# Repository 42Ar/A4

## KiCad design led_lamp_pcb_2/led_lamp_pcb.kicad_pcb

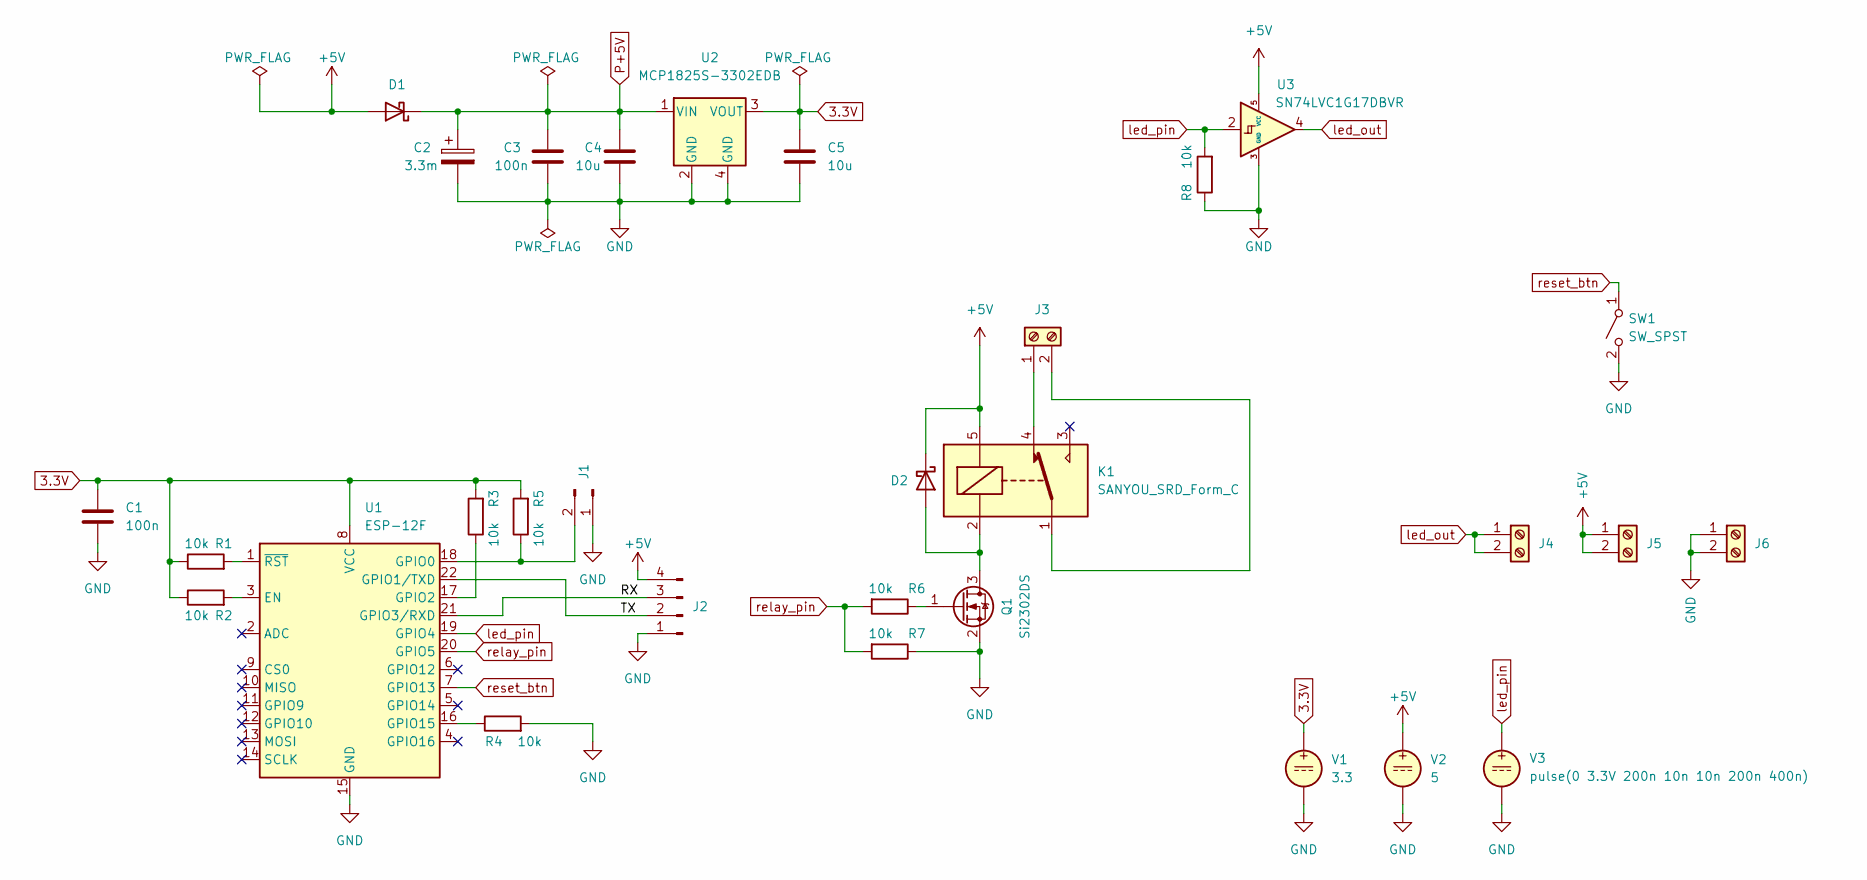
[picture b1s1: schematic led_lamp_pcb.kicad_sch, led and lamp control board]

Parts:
C1, C3: 100n; C_0805_2012Metric_Pad1.18x1.45mm_HandSolder
C2: 3.3m; CP_Radial_D10.0mm_P5.00mm
C4, C5: 10u; C_0805_2012Metric_Pad1.18x1.45mm_HandSolder
D1, D2: 1N5817; D_SMA_Handsoldering
J1: Conn_01x02_Male; PinHeader_1x02_P2.54mm_Vertical
J2: Conn_01x04_Male; PinHeader_1x04_P2.54mm_Vertical
J3, J4, J5, J6: Screw_Terminal_01x02; TerminalBlock_bornier-2_P5.08mm
K1: SANYOU_SRD_Form_C; Relay_SPDT_SANYOU_SRD_Series_Form_C
Q1: Si2302DS; SOT-23_Handsoldering
R1, R2, R3, R4, R5, R6, R7, R8: 10k; R_0805_2012Metric_Pad1.20x1.40mm_HandSolder
SW1: SW_SPST; SW_Push_1P1T_NO_6x6mm_H9.5mm
U1: ESP-12F; ESP-12E
U2: MCP1825S-3302EDB; SOT-223
U3: SN74LVC1G17DBVR; SOT-23-5_HandSoldering
V1, V2, V3: VDC

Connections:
3.3V: C1.1, C5.1, R1.1, R2.1, R3.2, R5.2, U1.8 (VCC), U2.3 (VOUT), V1.1
+5V: D1.2 (A), D2.1 (K), J2.4, J5.1, J5.2, K1.5, U3.5 (VCC), V2.1
/RX: J2.3, U1.21 (GPIO3/RXD)
/TX: J2.2, U1.22 (GPIO1/TXD)
GND: C1.2, C2.2, C3.2, C4.2, C5.2, J1.1, J2.1, J6.1, J6.2, Q1.2 (S), R4.2, R7.1, R8.1, SW1.2 (B), U1.15 (GND), U2.2 (GND), U2.4 (GND), U3.3 (GND), V1.2, V2.2, V3.2
unnamed: D2.2 (A), K1.2, Q1.3 (D)
unnamed: J1.2, R5.1, U1.18 (GPIO0)
unnamed: J3.1, K1.4
unnamed: J3.2, K1.1
unnamed: Q1.1 (G), R6.1
unnamed: R1.2, U1.1 (~RST)
unnamed: R2.2, U1.3 (EN)
unnamed: R3.1, U1.17 (GPIO2)
unnamed: R4.1, U1.16 (GPIO15)
P+5V: C2.1, C3.1, C4.1, D1.1 (K), U2.1 (VIN)
led_out: J4.1, J4.2, U3.4
led_pin: R8.2, U1.19 (GPIO4), U3.2, V3.1
relay_pin: R6.2, R7.2, U1.20 (GPIO5)
reset_btn: SW1.1 (A), U1.7 (GPIO13)

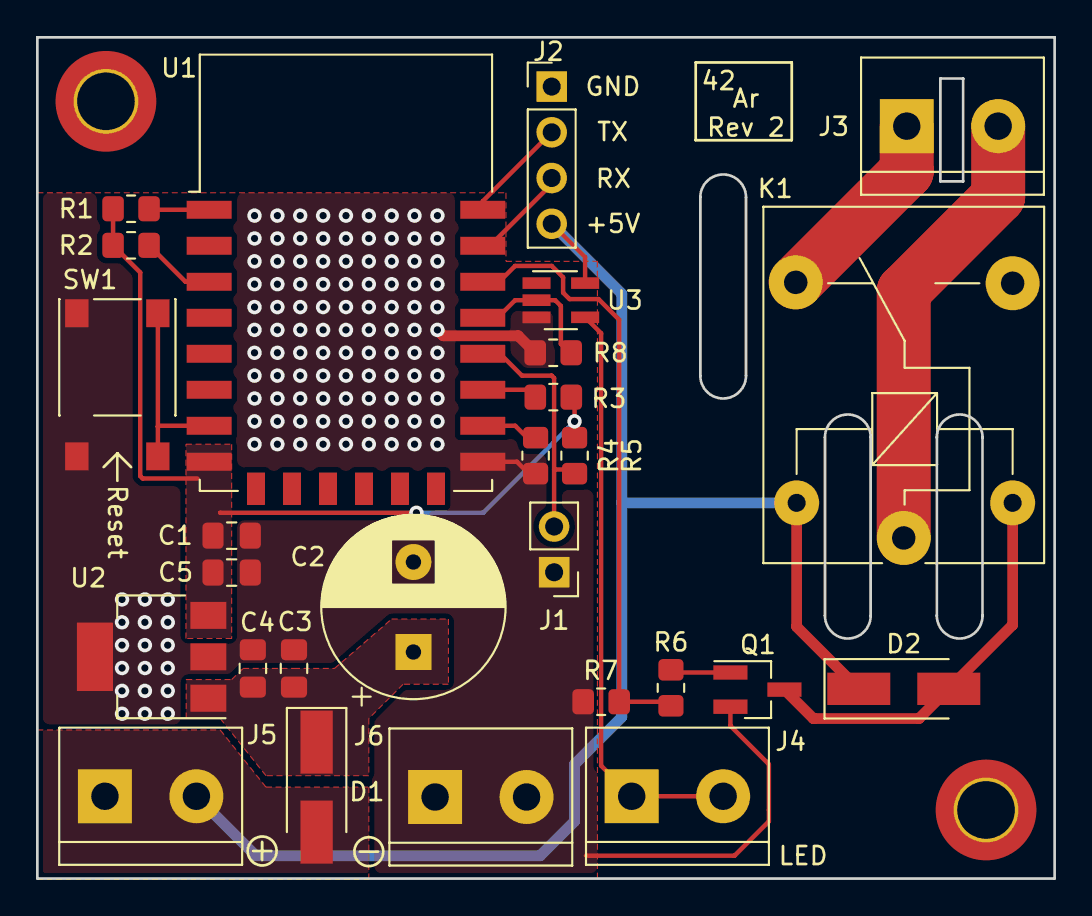
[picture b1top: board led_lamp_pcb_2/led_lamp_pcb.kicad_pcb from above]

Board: 2 copper layers, 56.5 x 46.7 mm, 29 parts (0 on the bottom side), 19 nets.

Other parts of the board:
H1, H2: MountingHole_3.2mm_M3_DIN965_Pad_TopBottom

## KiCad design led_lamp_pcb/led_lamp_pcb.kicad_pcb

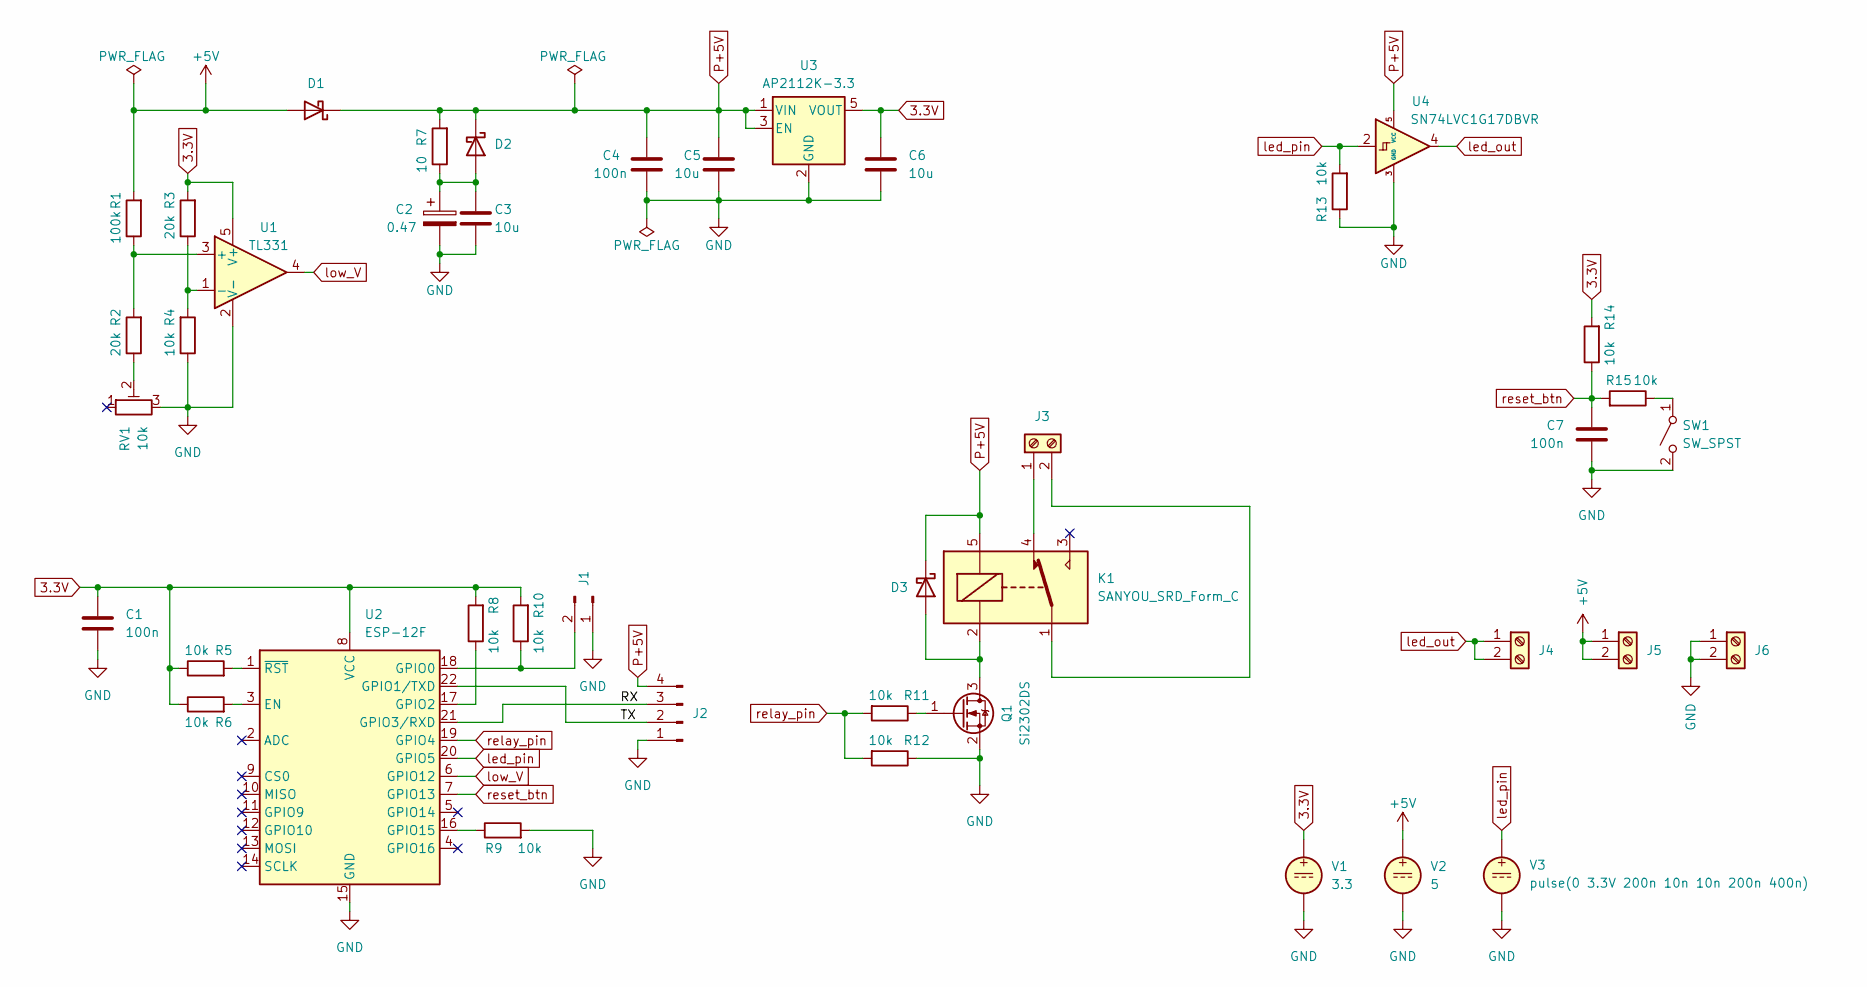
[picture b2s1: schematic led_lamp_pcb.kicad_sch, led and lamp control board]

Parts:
C1, C4, C7: 100n; C_0805_2012Metric_Pad1.18x1.45mm_HandSolder
C2: 0.47; CHP5R5L504R-TW
C3, C5, C6: 10u; C_0805_2012Metric_Pad1.18x1.45mm_HandSolder
D1, D2, D3: 1N5817; D_SMA_Handsoldering
J1: Conn_01x02_Male; PinHeader_1x02_P2.54mm_Vertical
J2: Conn_01x04_Male; PinHeader_1x04_P2.54mm_Vertical
J3, J4, J5, J6: Screw_Terminal_01x02; TerminalBlock_bornier-2_P5.08mm
K1: SANYOU_SRD_Form_C; Relay_SPDT_SANYOU_SRD_Series_Form_C
Q1: Si2302DS; SOT-23_Handsoldering
R1: 100k; R_0805_2012Metric_Pad1.20x1.40mm_HandSolder
R2, R3: 20k; R_0805_2012Metric_Pad1.20x1.40mm_HandSolder
R4, R5, R6, R8, R9, R10, R11, R12, R13, R14, R15: 10k; R_0805_2012Metric_Pad1.20x1.40mm_HandSolder
R7: 10; R_Axial_DIN0207_L6.3mm_D2.5mm_P7.62mm_Horizontal
RV1: 10k; Potentiometer_Piher_PT-10-V05_Vertical
SW1: SW_SPST; SW_Push_1P1T_NO_6x6mm_H9.5mm
U1: TL331; SOT-23-5_HandSoldering
U2: ESP-12F; ESP-12E
U3: AP2112K-3.3; SOT-23-5_HandSoldering
U4: SN74LVC1G17DBVR; SOT-23-5_HandSoldering
V1, V2, V3: VDC

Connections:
3.3V: C1.1, C6.1, R3.2, R5.1, R6.1, R8.2, R10.2, R14.2, U1.5 (V+), U2.8 (VCC), U3.5 (VOUT), V1.1
+5V: D1.2 (A), J5.1, J5.2, R1.2, V2.1
/RX: J2.3, U2.21 (GPIO3/RXD)
/TX: J2.2, U2.22 (GPIO1/TXD)
GND: C1.2, C2.2, C3.2, C4.2, C5.2, C6.2, C7.2, J1.1, J2.1, J6.1, J6.2, Q1.2 (S), R4.1, R9.2, R12.1, R13.1, RV1.3, SW1.2 (B), U1.2 (V-), U2.15 (GND), U3.2 (GND), U4.3 (GND), V1.2, V2.2, V3.2
unnamed: C2.1, C3.1, D2.2 (A), R7.1
unnamed: D3.2 (A), K1.2, Q1.3 (D)
unnamed: J1.2, R10.1, U2.18 (GPIO0)
unnamed: J3.1, K1.4
unnamed: J3.2, K1.1
unnamed: Q1.1 (G), R11.1
unnamed: R1.1, R2.2, U1.3 (+)
unnamed: R2.1, RV1.2
unnamed: R3.1, R4.2, U1.1 (-)
unnamed: R5.2, U2.1 (~RST)
unnamed: R6.2, U2.3 (EN)
unnamed: R8.1, U2.17 (GPIO2)
unnamed: R9.1, U2.16 (GPIO15)
unnamed: R15.1, SW1.1 (A)
P+5V: C4.1, C5.1, D1.1 (K), D2.1 (K), D3.1 (K), J2.4, K1.5, R7.2, U3.1 (VIN), U3.3 (EN), U4.5 (VCC)
led_out: J4.1, J4.2, U4.4
led_pin: R13.2, U2.20 (GPIO5), U4.2, V3.1
low_V: U1.4, U2.6 (GPIO12)
relay_pin: R11.2, R12.2, U2.19 (GPIO4)
reset_btn: C7.1, R14.1, R15.2, U2.7 (GPIO13)

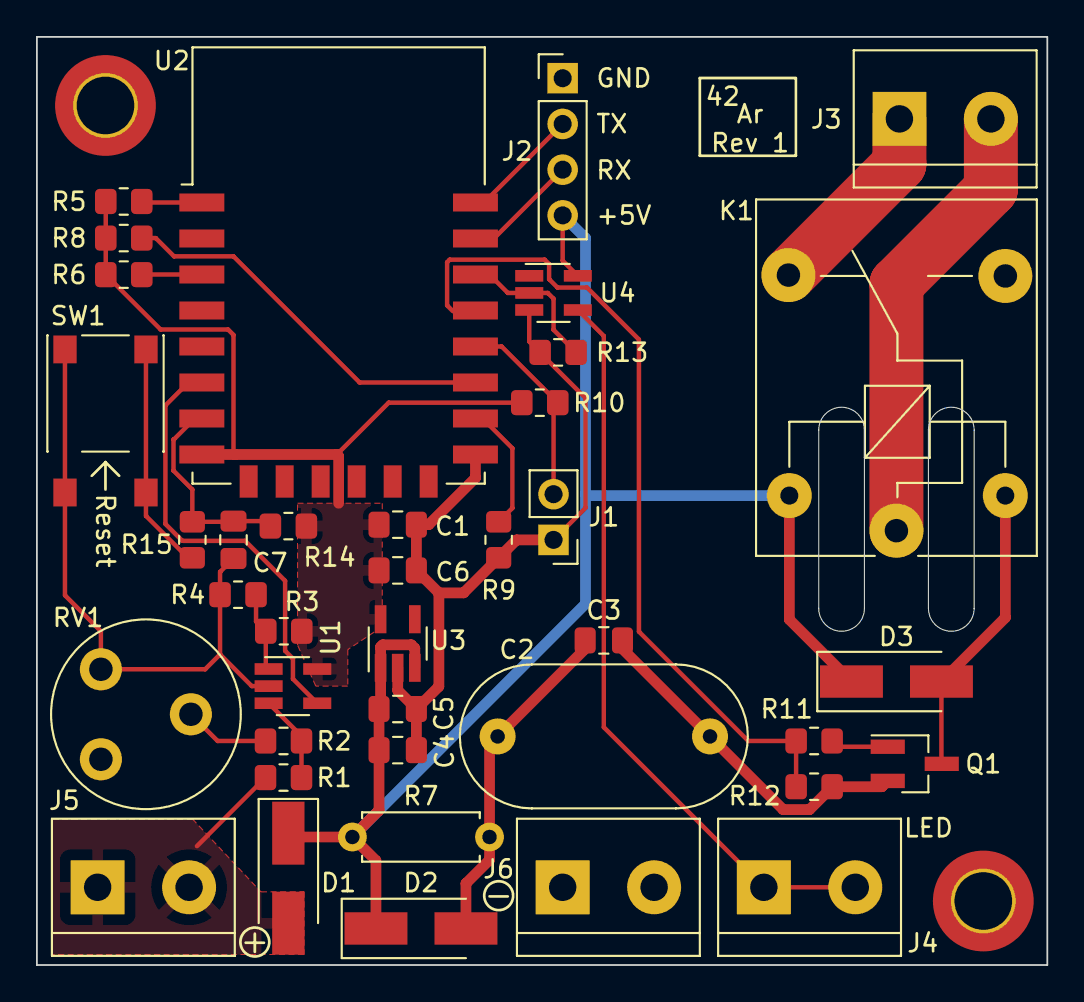
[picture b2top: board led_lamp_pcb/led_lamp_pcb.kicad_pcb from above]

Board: 2 copper layers, 56.1 x 51.6 mm, 41 parts (0 on the bottom side), 25 nets.

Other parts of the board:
H1, H2: MountingHole_3.2mm_M3_DIN965_Pad_TopBottom

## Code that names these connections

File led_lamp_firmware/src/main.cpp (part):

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#define BRAND      "A4-IOT"

//=== old board
// #define RELAY_PIN D5
// #define LED_PIN D6

//=== new board
#define RELAY_PIN 5u
#define LED_PIN 4u
#define RESET_BTN_PIN 13u
#define DISABLE_LOGGING


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#define PERF_REPORT_INTERVAL 20e3


Adafruit_NeoPixel strip(LED_COUNT, LED_PIN, NEO_RGB + NEO_KHZ800);
HomieNode node("lamp", "Lamp", "lamp");
float temp = -100;
float effect_speed = 1;
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  if(main_on){
    set_effect(0);
  }
  digitalWrite(RELAY_PIN, !main_on);
  node.setProperty("main").send(main_on?"true":"false");
}

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}

void setup(){
  pinMode(RELAY_PIN, OUTPUT);
  digitalWrite(RELAY_PIN, 0);
  
  color = ints_to_color(255, 255, 255);
  strip.begin();
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#endif
  Homie_setBrand(BRAND);
  Homie_setFirmware(FW_NAME, FW_VERSION);
#ifdef RESET_BTN_PIN
  Homie.setResetTrigger(RESET_BTN_PIN, LOW, 2000);
#else
  Homie.disableResetTrigger();
#endif
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
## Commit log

2022-07-22 first successfull tests with temp calculation
2022-07-30 refactor to use platform IO
2022-07-30 refactor
2022-07-30 deleted unnecessary files
2022-09-29 current version
2022-10-03 the board v1.0
2022-10-09 rev 1 as send to manufacturer
2022-10-12 add new effect
2022-10-24 remove none sleep mode
2022-11-01 switch to v3
2022-11-01 add lemon light config gen
2022-11-01 removed obsolete temp feature
2022-11-01 add missing generated config
2022-12-09 add xmas mode and layout for new boards
2022-12-09 add version 2 design of pcb, as end to the manufacturer
2023-01-08 new board layout
2023-01-08 refactor for clarity
2023-02-14 add better knob project
2023-08-05 add fridge door handle
2023-08-05 add tags and microwave door handle
2024-10-16 frame handler; untested
2024-10-26 Added additional .gitignore exceptions
